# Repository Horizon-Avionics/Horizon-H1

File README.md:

# Horizon Avionics

## Building a fully open-source flight computer.

### Hardware By @Scooter Y, and @Meddy B.
### Software By: @Stars, and @Chocowafer

------

#### About:

The Goal of Horizon Avionics is to be able to build a full-fledged, and open-source flight computer for amateur rocketry. There is no such board online, and we are hoping for this board to streamline open-sourcing products instead of charging upwards of $400 for a ~$130 board.

#### Features:

- This whole board including antennas are under $150 USD.

- IMU/Baro for our sensor data.

- GPS for navigation of where the rocket landed and it's flight path.

- RF - Including a transmit tower for receiving/sending data from the rocket live during the flight.

- NAND + Micro SD Card Storage for logging.

- 3 MCU's each controlling different ascpetcs of the flight computer- MMCU, TMCU, NMCU.

- H-Bridge for servo movement.

- Working PWM for TVC and/or Reaction Wheel

- Pyro-channels for parachute deployment

  ------

#### How it's all gonna work:

For the most part, this will all be explained over on the software repo, but a short synopsis will be provided below.

In short, we have 3 micro-controllers, the MMCU, the TMCU, and the NMCU. Each one of these MCU's is responsible for a different aspect of the functionality of the flight computer.  

- **The TMCU**

​	The TMCU is responsible for a number of different things. It takes in all the raw data from the IMU, Baro and the GPS data and sending it to the MMCU via SPI for filtering and logging. It is also resposible for sending and receiving the radio packets. In-short, the TMCU does a lot of different things for this board to make room for the MMCU to do the heavy lifting.

- **The NMCU**

  The NMCU is responsible for more of the physical actions of the rocket. It's main jobs are to on boot, load the saved state, for position movements, and while in-flight, it's jobs are to take in the filtered data from the MMCU, and use it to control the Camera, servo lines, reaction wheel, and pyro-channels.

- **The MMCU**

  The MMCU is our main MCU. It's main responsibilities are to, while in flight, take in all the data from the TMCU, put it through a filter (we will be using the Kalman Filter for our board as it is the best one we have found to remove noise and such), package the data, and send it back off to the TMCU for radio sending or to the NMCU for movments. Along with sending it to the nessecary MCU's, it also sends the packaged, and filtered data to the NAND which will eventually be moved to the SD Card + the Camera footage upon landing.

------

#### Getting Started

To view the different changes between commits, check it out over on [CADLAB.io](https://cadlab.io/project/29344).

##### Checkout locally

1. `git clone https://github.com/Horizon-Avionics/Horizon-Avionics-Hardware`

2. Open the corresponding folder in KiCad 9.0

### Some Photos So Far

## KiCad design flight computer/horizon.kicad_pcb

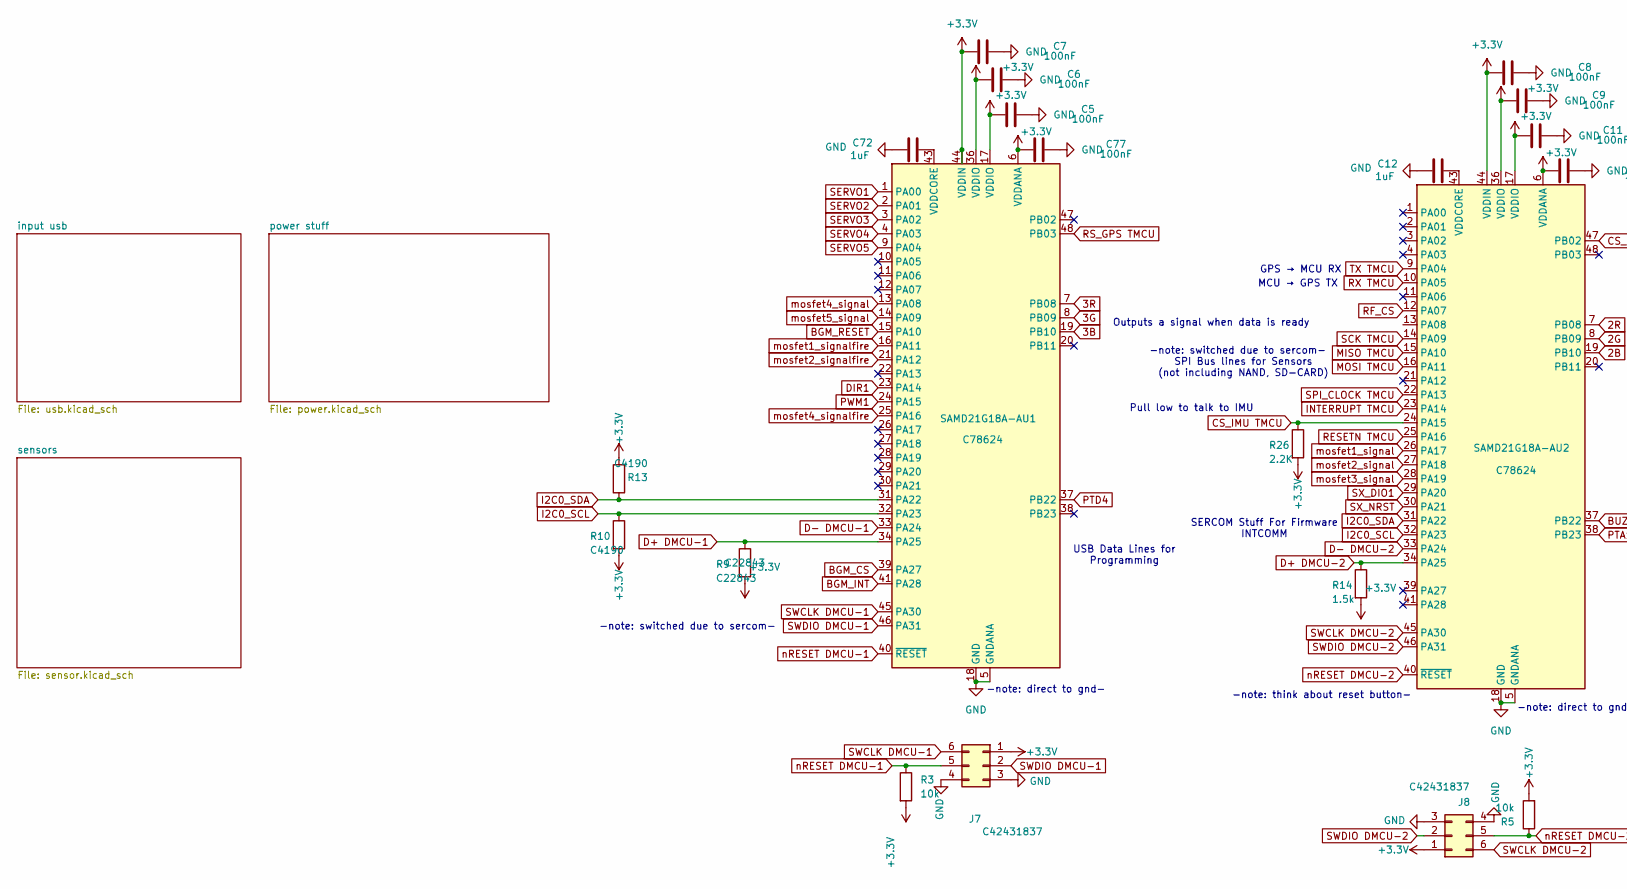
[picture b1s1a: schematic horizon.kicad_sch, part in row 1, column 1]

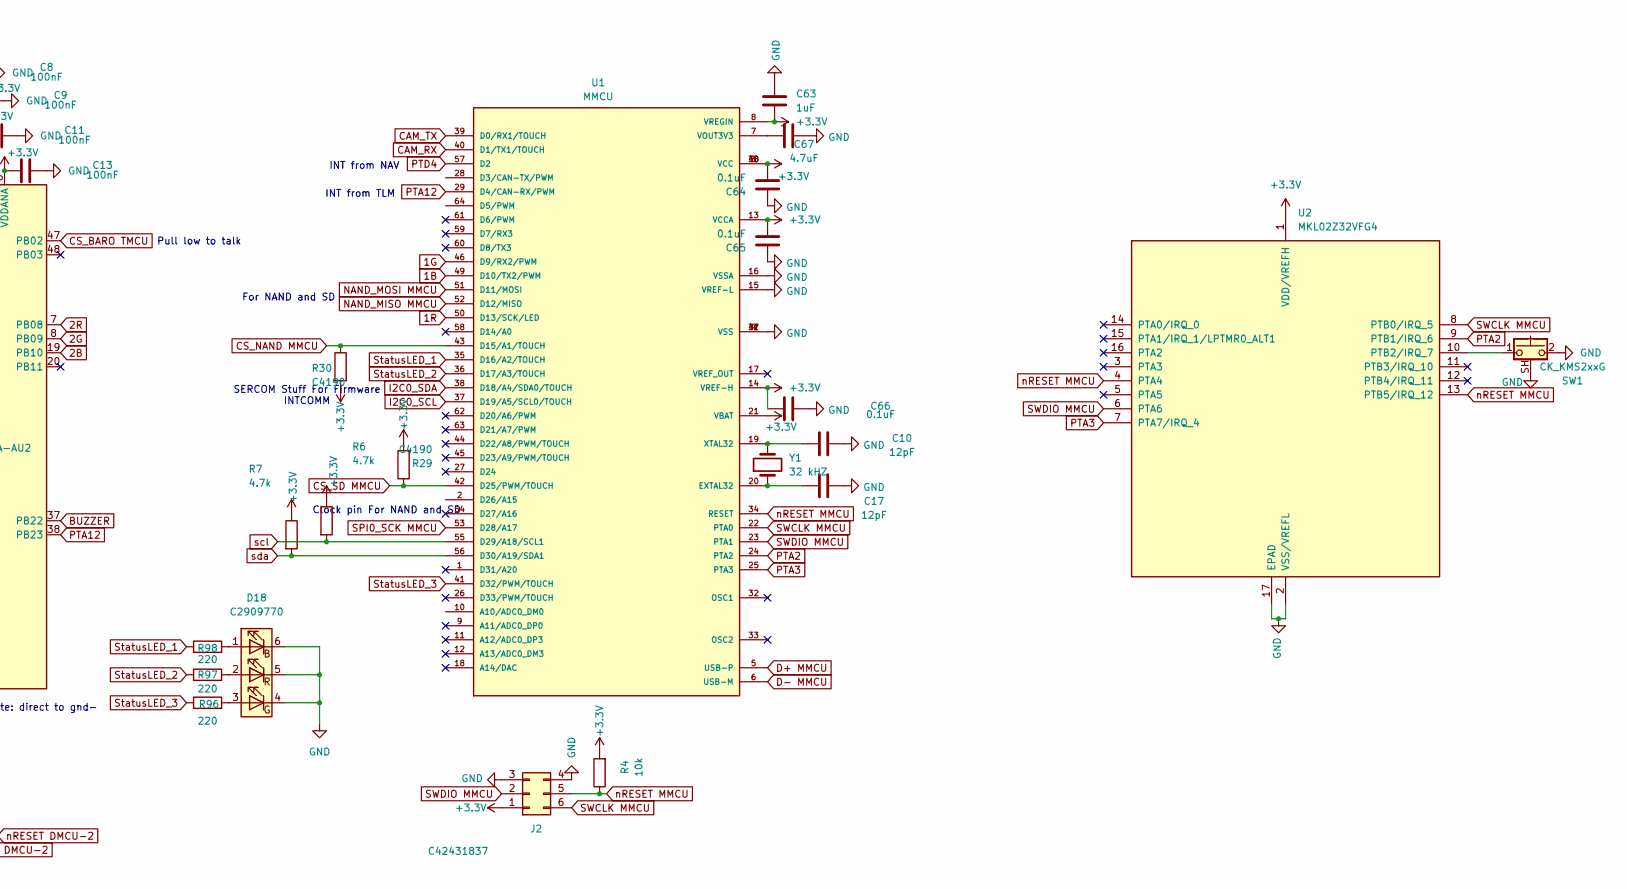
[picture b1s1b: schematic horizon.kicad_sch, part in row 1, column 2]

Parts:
C5, C6, C7, C8, C9, C11, C13, C77: 100nF; C_0603_1608Metric
C10, C17: 12pF; C_0603_1608Metric
C12, C63, C72: 1uF; C_0603_1608Metric
C64, C65, C66: 0.1uF; C_0603_1608Metric
C67: 4.7uF; C_0603_1608Metric
D18: C2909770; LED_ROHM_SMLVN6
J2, J7, J8: C42431837; PinHeader_2x03_P2.54mm_Vertical
R3, R4, R5: 10k; R_0603_1608Metric
R6, R7: 4.7k; R_0603_1608Metric
R9: C22843; R_0603_1608Metric; LCSC C22843
R10, R13, R29, R30: C4190; R_0603_1608Metric
R14: 1.5k; R_0603_1608Metric
R26: 2.2K; R_0603_1608Metric
R96, R97, R98: 220; R_0603_1608Metric
SAMD21G18A-AU1, SAMD21G18A-AU2: C78624; TQFP-48_7x7mm_P0.5mm
SW1: CK_KMS2xxG; SW_SPST_CK_KMS2xxGP
U1: MMCU; QFP50P1200X1200X160-64N
U2: MKL02Z32VFG4; QFN-16-1EP_3x3mm_P0.5mm_EP1.9x1.9mm
Y1: 32 kHZ; Crystal_AT310_D3.0mm_L10.0mm_Vertical

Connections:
1B: U1.49 (D10/TX2/PWM); also elsewhere on the board
1G: U1.46 (D9/RX2/PWM); also elsewhere on the board
1R: U1.50 (D13/SCK/LED); also elsewhere on the board
2B: SAMD21G18A-AU2.19 (PB10); also elsewhere on the board
2G: SAMD21G18A-AU2.8 (PB09); also elsewhere on the board
2R: SAMD21G18A-AU2.7 (PB08); also elsewhere on the board
3B: SAMD21G18A-AU1.19 (PB10); also elsewhere on the board
3G: SAMD21G18A-AU1.8 (PB09); also elsewhere on the board
3R: SAMD21G18A-AU1.7 (PB08); also elsewhere on the board
+3.3V: C5.2, C6.2, C7.2, C8.2, C9.2, C11.2, C13.2, C63.1, C64.1, C65.1, C66.1, C77.2, J2.1, J7.1, J8.1, R3.2, R4.2, R5.2, R6.1, R7.1, R9.2, R10.2, R13.2, R14.2, R26.2, R29.2, R30.2, SAMD21G18A-AU1.6 (VDDANA), SAMD21G18A-AU1.17 (VDDIO), SAMD21G18A-AU1.36 (VDDIO), SAMD21G18A-AU1.44 (VDDIN), SAMD21G18A-AU2.6 (VDDANA), SAMD21G18A-AU2.17 (VDDIO), SAMD21G18A-AU2.36 (VDDIO), SAMD21G18A-AU2.44 (VDDIN), U1.3 (VCC), U1.8 (VREGIN), U1.13 (VCCA), U1.14 (VREF-H), U1.21 (VBAT), U1.30 (VCC), U1.48 (VCC), U2.1 (VDD/VREFH); also elsewhere on the board
BGM_CS: SAMD21G18A-AU1.39 (PA27); also elsewhere on the board
BGM_INT: SAMD21G18A-AU1.41 (PA28); also elsewhere on the board
BGM_RESET: SAMD21G18A-AU1.15 (PA10); also elsewhere on the board
BUZZER: SAMD21G18A-AU2.37 (PB22); also elsewhere on the board
CAM_RX: U1.40 (D1/TX1/TOUCH); also elsewhere on the board
CAM_TX: U1.39 (D0/RX1/TOUCH); also elsewhere on the board
CS_BARO TMCU: SAMD21G18A-AU2.47 (PB02); also elsewhere on the board
CS_IMU TMCU: R26.1, SAMD21G18A-AU2.24 (PA15); also elsewhere on the board
CS_NAND MMCU: R30.1, U1.43 (D15/A1/TOUCH); also elsewhere on the board
CS_SD MMCU: R29.1, U1.42 (D25/PWM/TOUCH); also elsewhere on the board
D+ DMCU-1: R9.1, SAMD21G18A-AU1.34 (PA25); also elsewhere on the board
D+ DMCU-2: R14.1, SAMD21G18A-AU2.34 (PA25); also elsewhere on the board
D+ MMCU: U1.5 (USB-P); also elsewhere on the board
D- DMCU-1: SAMD21G18A-AU1.33 (PA24); also elsewhere on the board
D- DMCU-2: SAMD21G18A-AU2.33 (PA24); also elsewhere on the board
D- MMCU: U1.6 (USB-M); also elsewhere on the board
DIR1: SAMD21G18A-AU1.23 (PA14)
GND: C5.1, C6.1, C7.1, C8.1, C9.1, C10.2, C11.1, C12.1, C13.1, C17.2, C63.2, C64.2, C65.2, C66.2, C67.2, C72.1, C77.1, D18.4 (GK), D18.5 (RK), D18.6 (BK), J2.3, J2.4, J7.3, J7.4, J8.3, J8.4, SAMD21G18A-AU1.5 (GNDANA), SAMD21G18A-AU1.18 (GND), SAMD21G18A-AU1.35 (GND), SAMD21G18A-AU1.42 (GND), SAMD21G18A-AU2.5 (GNDANA), SAMD21G18A-AU2.18 (GND), SAMD21G18A-AU2.35 (GND), SAMD21G18A-AU2.42 (GND), SW1.2, SW1.SH (B), U1.4 (VSS), U1.15 (VREF-L), U1.16 (VSSA), U1.31 (VSS), U1.47 (VSS), U2.2 (VSS/VREFL), U2.17 (EPAD); also elsewhere on the board
I2C0_SCL: R10.1, SAMD21G18A-AU1.32 (PA23), SAMD21G18A-AU2.32 (PA23), U1.37 (D19/A5/SCL0/TOUCH); also elsewhere on the board
I2C0_SDA: R13.1, SAMD21G18A-AU1.31 (PA22), SAMD21G18A-AU2.31 (PA22), U1.38 (D18/A4/SDA0/TOUCH); also elsewhere on the board
INTERRUPT TMCU: SAMD21G18A-AU2.23 (PA14); also elsewhere on the board
MISO TMCU: SAMD21G18A-AU2.15 (PA10); also elsewhere on the board
MOSI TMCU: SAMD21G18A-AU2.16 (PA11); also elsewhere on the board
NAND_MISO MMCU: U1.52 (D12/MISO); also elsewhere on the board
NAND_MOSI MMCU: U1.51 (D11/MOSI); also elsewhere on the board
unnamed: D18.1 (BA), R98.2
unnamed: D18.3 (GA), R96.2
unnamed: D18.2 (RA), R97.2
unnamed: C72.2, SAMD21G18A-AU1.43 (VDDCORE)
unnamed: C12.2, SAMD21G18A-AU2.43 (VDDCORE)
unnamed: C17.1, U1.20 (EXTAL32), Y1.1
unnamed: C67.1, U1.7 (VOUT3V3)
unnamed: C10.1, U1.19 (XTAL32), Y1.2
unnamed: SW1.1, U2.10 (PTB2/IRQ_7)
PTA2: U1.24 (PTA2), U2.9 (PTB1/IRQ_6)
PTA3: U1.25 (PTA3), U2.7 (PTA7/IRQ_4)
PTA12: SAMD21G18A-AU2.38 (PB23), U1.29 (D4/CAN-RX/PWM)
PTD4: SAMD21G18A-AU1.37 (PB22), U1.57 (D2)
PWM1: SAMD21G18A-AU1.24 (PA15)
RESETN TMCU: SAMD21G18A-AU2.25 (PA16)
RF_CS: SAMD21G18A-AU2.12 (PA07); also elsewhere on the board
RS_GPS TMCU: SAMD21G18A-AU1.48 (PB03); also elsewhere on the board
RX TMCU: SAMD21G18A-AU2.10 (PA05); also elsewhere on the board
SCK TMCU: SAMD21G18A-AU2.14 (PA09); also elsewhere on the board
SERVO1: SAMD21G18A-AU1.1 (PA00); also elsewhere on the board
SERVO2: SAMD21G18A-AU1.2 (PA01); also elsewhere on the board
SERVO3: SAMD21G18A-AU1.3 (PA02); also elsewhere on the board
SERVO4: SAMD21G18A-AU1.4 (PA03); also elsewhere on the board
SERVO5: SAMD21G18A-AU1.9 (PA04); also elsewhere on the board
SPI0_SCK MMCU: U1.53 (D28/A17); also elsewhere on the board
SPI_CLOCK TMCU: SAMD21G18A-AU2.22 (PA13); also elsewhere on the board
SWCLK DMCU-1: J7.6, SAMD21G18A-AU1.45 (PA30)
SWCLK DMCU-2: J8.6, SAMD21G18A-AU2.45 (PA30)
SWCLK MMCU: J2.6, U1.22 (PTA0), U2.8 (PTB0/IRQ_5)
SWDIO DMCU-1: J7.2, SAMD21G18A-AU1.46 (PA31)
SWDIO DMCU-2: J8.2, SAMD21G18A-AU2.46 (PA31)
SWDIO MMCU: J2.2, U1.23 (PTA1), U2.6 (PTA6)
SX_DIO1: SAMD21G18A-AU2.29 (PA20); also elsewhere on the board
SX_NRST: SAMD21G18A-AU2.30 (PA21); also elsewhere on the board
StatusLED_1: R98.1, U1.35 (D16/A2/TOUCH)
StatusLED_2: R97.1, U1.36 (D17/A3/TOUCH)
StatusLED_3: R96.1, U1.41 (D32/PWM/TOUCH)
TX TMCU: SAMD21G18A-AU2.9 (PA04); also elsewhere on the board
mosfet1_signal: SAMD21G18A-AU2.26 (PA17)
mosfet1_signalfire: SAMD21G18A-AU1.16 (PA11); also elsewhere on the board
mosfet2_signal: SAMD21G18A-AU2.27 (PA18)
mosfet2_signalfire: SAMD21G18A-AU1.21 (PA12); also elsewhere on the board
mosfet3_signal: SAMD21G18A-AU2.28 (PA19)
mosfet4_signal: SAMD21G18A-AU1.13 (PA08)
mosfet4_signalfire: SAMD21G18A-AU1.25 (PA16)
mosfet5_signal: SAMD21G18A-AU1.14 (PA09)
nRESET DMCU-1: J7.5, R3.1, SAMD21G18A-AU1.40 (~RESET)
nRESET DMCU-2: J8.5, R5.1, SAMD21G18A-AU2.40 (~RESET)
nRESET MMCU: J2.5, R4.1, U1.34 (RESET), U2.4 (PTA4), U2.13 (PTB5/IRQ_12)
scl: R6.2, U1.55 (D29/A18/SCL1)
sda: R7.2, U1.56 (D30/A19/SDA1)

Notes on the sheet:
SERCOM Stuff For Firmware INTCOMM
-note: direct to gnd-
For NAND and SD
-note: switched due to sercom-
Pull low to talk to IMU
INT from TLM
Pull low to talk
GPS → MCU RX
Clock pin For NAND and SD
MCU → GPS TX
Outputs a signal when data is ready
-note: think about reset button-
INT from NAV
USB Data Lines for Programming
SPI Bus lines for Sensors (not including NAND, SD-CARD)

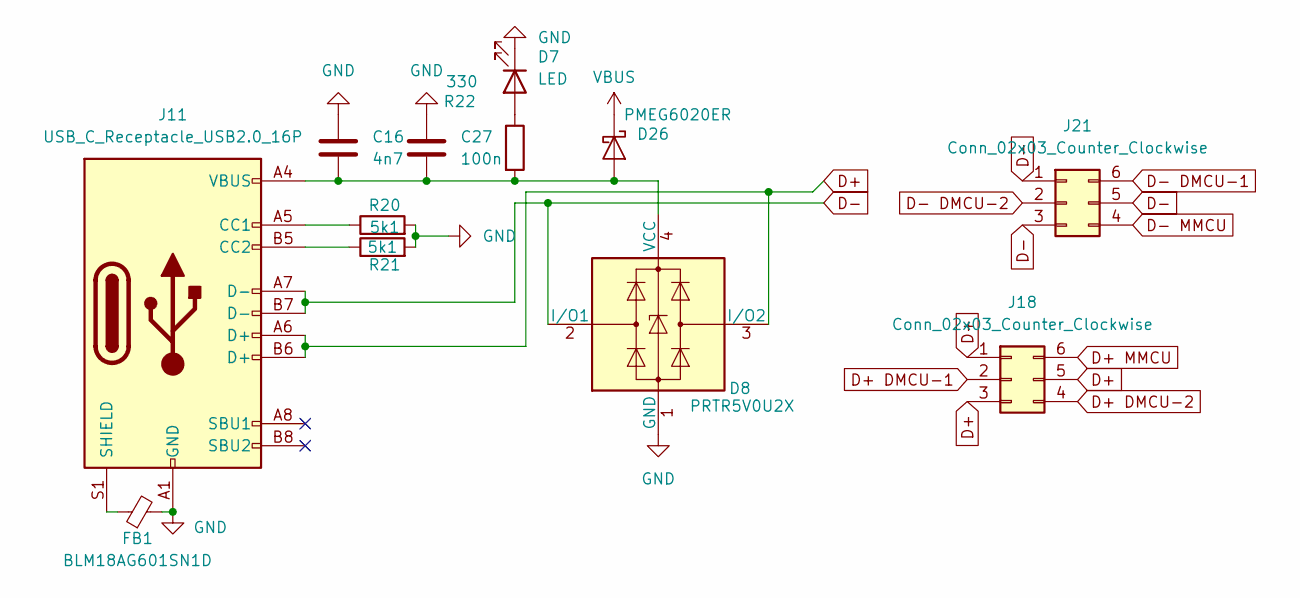
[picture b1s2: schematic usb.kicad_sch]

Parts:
C16: 4n7; C_0603_1608Metric
C27: 100n; C_0603_1608Metric
D7: LED; LED_0603_1608Metric
D8: PRTR5V0U2X; SOT-143
D26: PMEG6020ER; Nexperia_CFP3_SOD-123W
FB1: BLM18AG601SN1D; R_0603_1608Metric
J11: USB_C_Receptacle_USB2.0_16P; USB_C_Receptacle_GCT_USB4105-xx-A_16P_TopMnt_Horizontal
J18, J21: Conn_02x03_Counter_Clockwise; PinHeader_2x03_P2.54mm_Vertical
R20, R21: 5k1; R_0603_1608Metric
R22: 330; R_0603_1608Metric

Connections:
D+: D8.3 (I/O2), J11.A6 (D+), J11.B6 (D+), J18.1, J18.3, J18.5
D+ DMCU-1: J18.2; also elsewhere on the board
D+ DMCU-2: J18.4; also elsewhere on the board
D+ MMCU: J18.6; also elsewhere on the board
D-: D8.2 (I/O1), J11.A7 (D-), J11.B7 (D-), J21.1, J21.3, J21.5
D- DMCU-1: J21.6; also elsewhere on the board
D- DMCU-2: J21.2; also elsewhere on the board
D- MMCU: J21.4; also elsewhere on the board
GND: C16.1, C27.1, D7.1 (K), D8.1 (GND), FB1.2, J11.A1 (GND), J11.A12 (GND), J11.B1 (GND), J11.B12 (GND), R20.2, R21.2; also elsewhere on the board
unnamed: D7.2 (A), R22.1
unnamed: C16.2, C27.2, D8.4 (VCC), D26.2 (A), J11.A4 (VBUS), J11.A9 (VBUS), J11.B4 (VBUS), J11.B9 (VBUS), R22.2
unnamed: J11.A5 (CC1), R20.1
unnamed: J11.B5 (CC2), R21.1
unnamed: FB1.1, J11.S1 (SHIELD)
POWAAAA: D26.1 (K); also elsewhere on the board

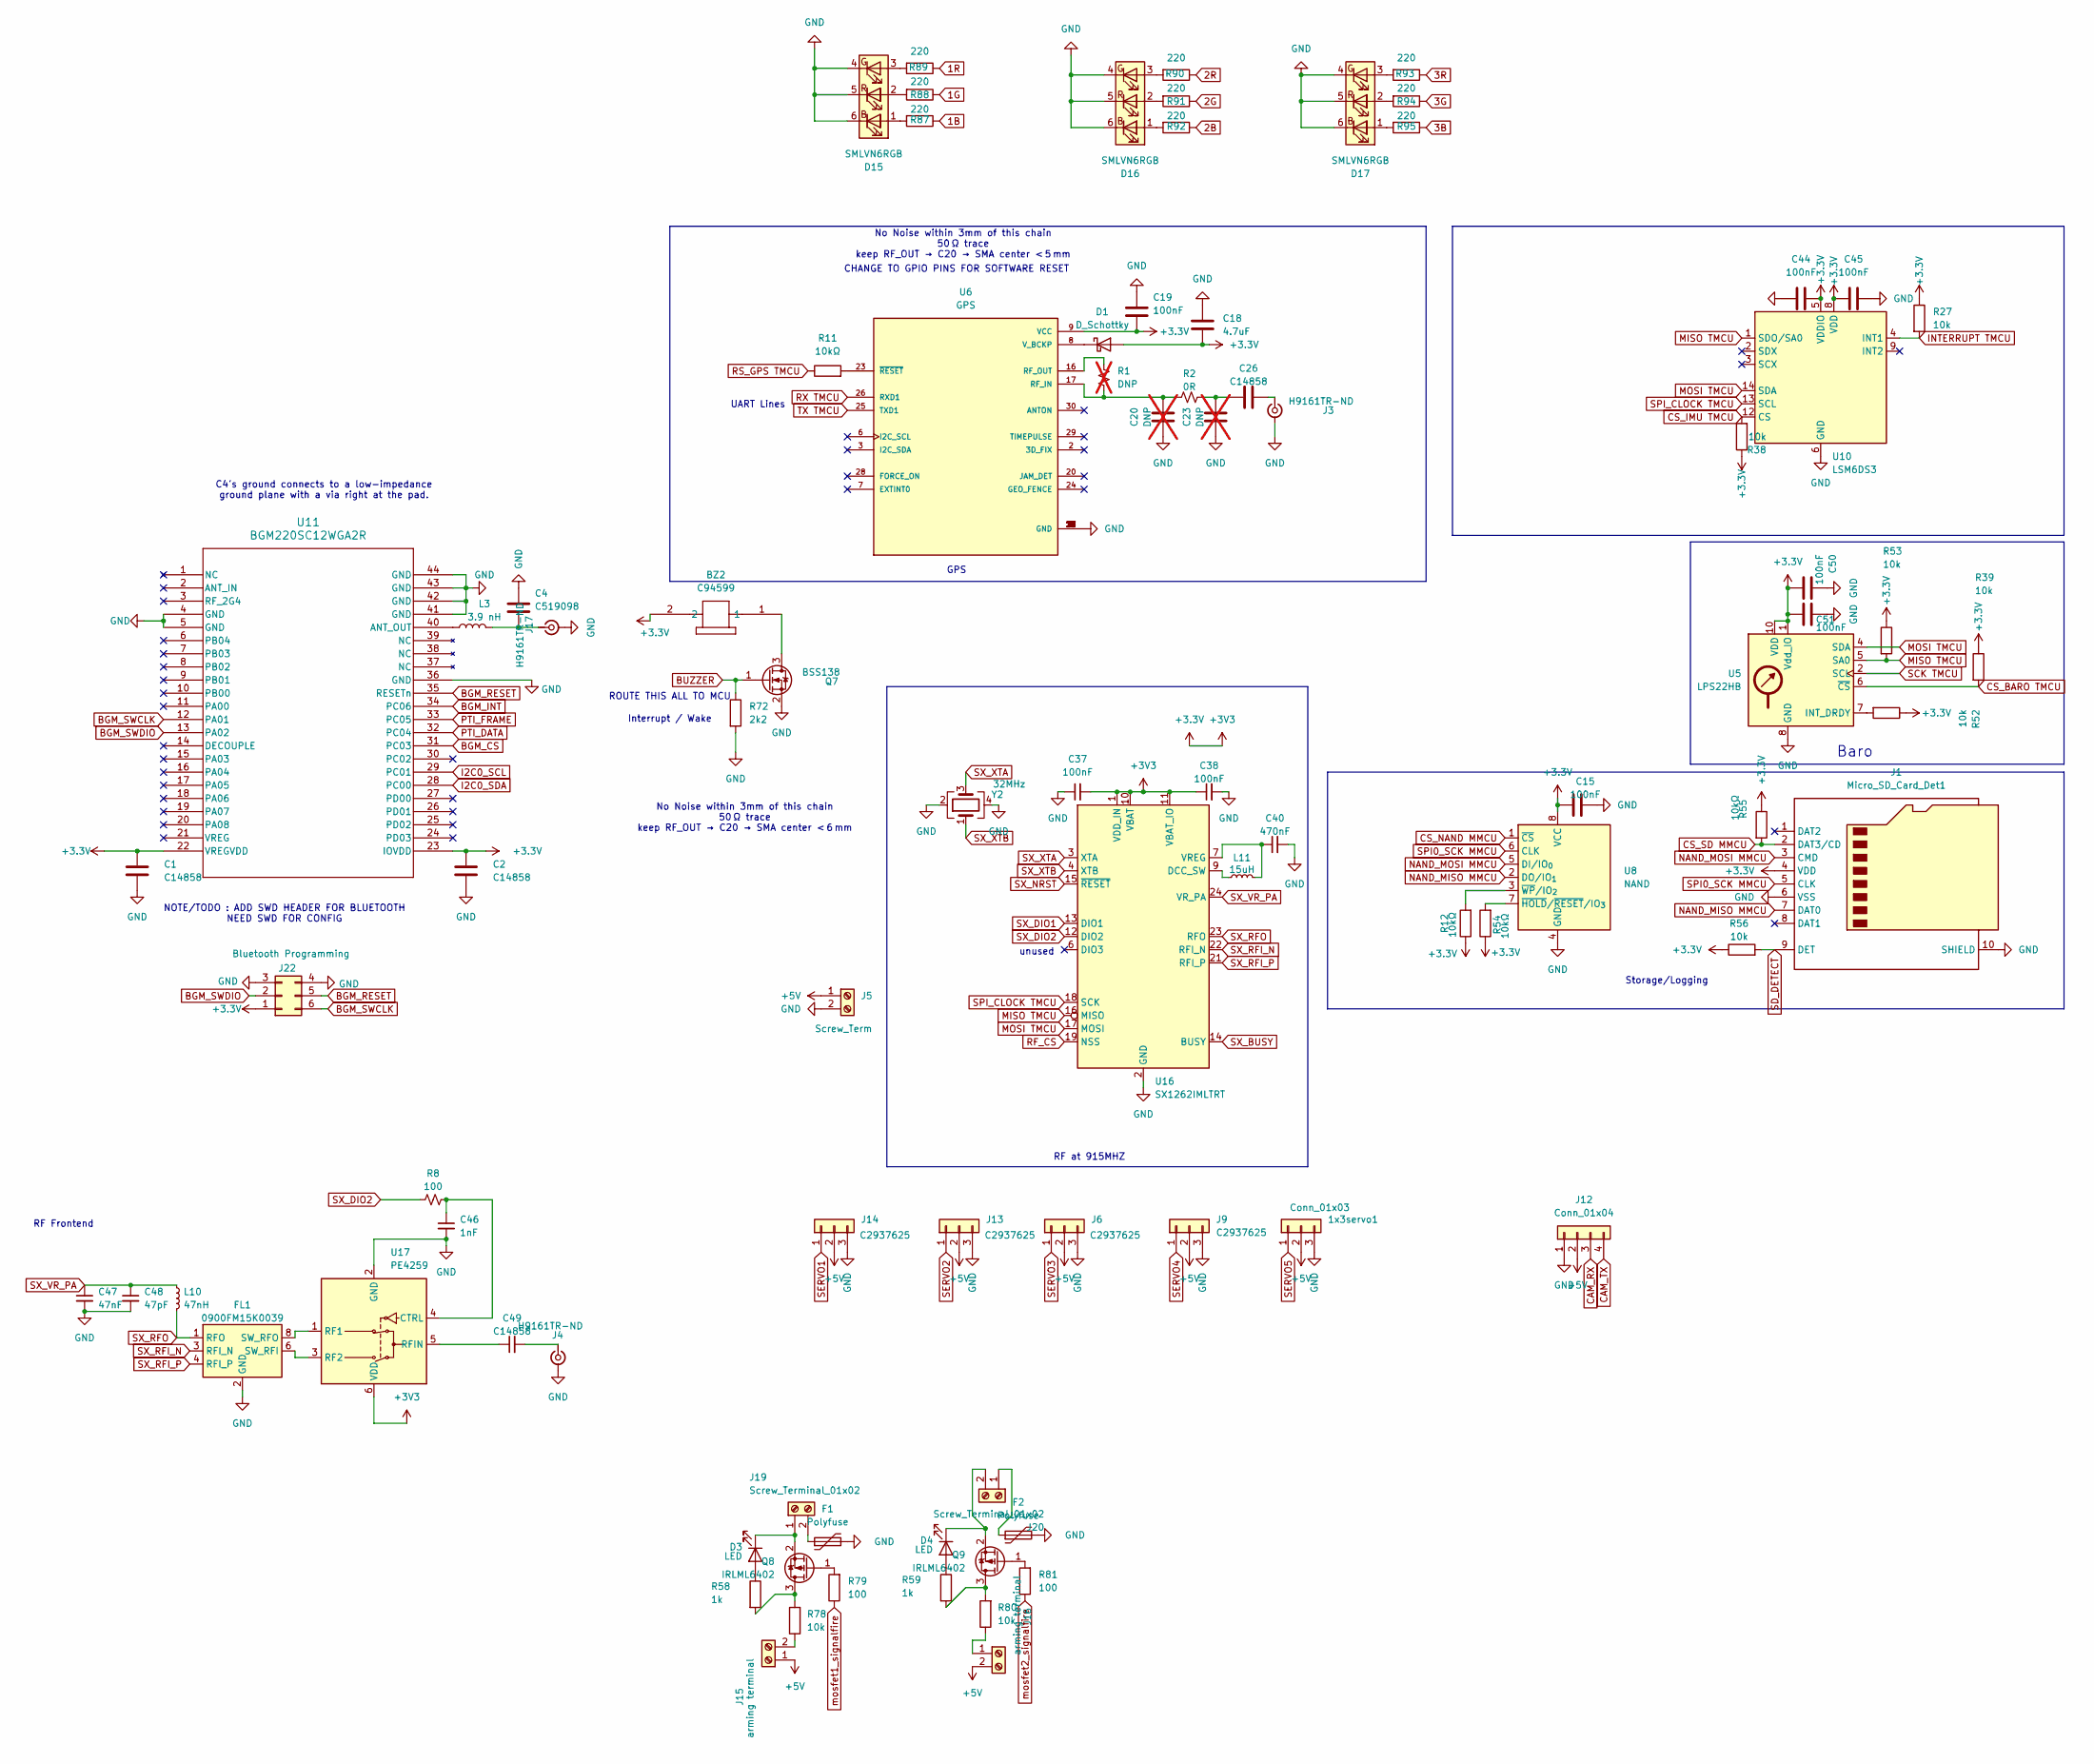
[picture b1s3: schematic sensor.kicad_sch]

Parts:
1x3servo1: Conn_01x03; PinHeader_1x03_P2.54mm_Vertical
BZ2: C94599; MLT-8530_JHE
C1, C2, C26: C14858; C_0603_1608Metric
C4: C519098; C_0603_1608Metric
C15, C19, C44, C45, C50, C51: 100nF; C_0603_1608Metric
C18: 4.7uF; C_0603_1608Metric
C20, C23: DNP; C_0603_1608Metric; not fitted
C37, C38: 100nF; C_0603_1608Metric; LCSC Part C14663
C40: 470nF; C_0603_1608Metric; LCSC Part C1623
C46: 1nF; C_0603_1608Metric; LCSC Part C100040
C47: 47nF; C_0603_1608Metric; LCSC Part C107093
C48: 47pF; C_0603_1608Metric; LCSC Part C105622
C49: C14858; C_0603_1608Metric; LCSC Part C14665
D1: D_Schottky; D_0603_1608Metric
D3, D4: LED; LED_0603_1608Metric
D15, D16, D17: SMLVN6RGB; LED_ROHM_SMLVN6
F1, F2: Polyfuse; Fuse_0603_1608Metric
FL1: 0900FM15K0039; Balun_Johanson_0900FM15K0039; LCSC Part C5224443
J1: Micro_SD_Card_Det1; microSD_HC_Hirose_DM3D-SF
J3, J4, J17: H9161TR-ND; U.FL_Hirose_U.FL-R-SMT-1_Vertical
J5: Screw_Term; TerminalBlock_Phoenix_MPT-0,5-2-2.54_1x02_P2.54mm_Horizontal
J6, J9, J13, J14: C2937625; PinHeader_1x03_P2.54mm_Vertical
J12: Conn_01x04; PinHeader_1x04_P2.54mm_Vertical
J15, J16: arming terminal; TerminalBlock_Phoenix_MPT-0,5-2-2.54_1x02_P2.54mm_Horizontal
J19, J20: Screw_Terminal_01x02; TerminalBlock_Phoenix_MPT-0,5-2-2.54_1x02_P2.54mm_Horizontal
J22: Bluetooth Programming; PinHeader_2x03_P2.54mm_Vertical
L3: 3.9 nH; L_0603_1608Metric
L10: 47nH; L_0603_1608Metric; LCSC Part C285885
L11: 15uH; L_0805_2012Metric; LCSC Part C383402
Q7: BSS138; SOT-23
Q8, Q9: IRLML6402; SOT-23
R1: DNP; R_0603_1608Metric; not fitted
R2: 0R; R_0603_1608Metric
R8: 100; R_0603_1608Metric; LCSC Part C105588
R11, R12, R54, R55: 10kΩ; R_0603_1608Metric
R27, R38, R39, R52, R53, R56, R78, R80: 10k; R_0603_1608Metric
R58, R59: 1k; R_0603_1608Metric
R72: 2k2; R_0603_1608Metric
R79, R81: 100; R_0603_1608Metric
R87, R88, R89, R90, R91, R92, R93, R94, R95: 220; R_0603_1608Metric
U5: LPS22HB; ST_HLGA-10_2x2mm_P0.5mm_LayoutBorder3x2y
U6: GPS; Quectel_L96; DigiKey_Part_Number 2958-L96-M33TR-ND
U8: NAND; SOIC-8_5.3x5.3mm_P1.27mm
U10: LSM6DS3; LGA-14_3x2.5mm_P0.5mm_LayoutBorder3x4y
U11: BGM220SC12WGA2R; BGM220S_SIL
U16: SX1262IMLTRT; QFN-24-1EP_4x4mm_P0.5mm_EP2.6x2.6mm; LCSC Part C191341
U17: PE4259; SOT-363_SC-70-6; LCSC Part C470892
Y2: 32MHz; Crystal_SMD_3225-4Pin_3.2x2.5mm; LCSC Part C37635386

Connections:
1B: R87.1; also elsewhere on the board
1G: R88.1; also elsewhere on the board
1R: R89.1; also elsewhere on the board
2B: R92.1; also elsewhere on the board
2G: R91.1; also elsewhere on the board
2R: R90.1; also elsewhere on the board
3B: R95.1; also elsewhere on the board
3G: R94.1; also elsewhere on the board
3R: R93.1; also elsewhere on the board
+3.3V: BZ2.2, C1.2, C2.2, C15.1, C18.2, C19.2, C37.2, C38.1, C44.2, C45.2, C50.2, C51.2, D1.2 (A), J1.4 (VDD), J22.1, R12.1, R27.1, R38.1, R39.1, R52.1, R53.1, R54.1, R55.1, R56.1, U5.1 (Vdd_IO), U5.10 (VDD), U6.9 (VCC), U8.8 (VCC), U10.5 (VDDIO), U10.8 (VDD), U11.22 (VREGVDD), U11.23 (IOVDD), U16.1 (VDD_IN), U16.10 (VBAT), U16.11 (VBAT_IO), U17.6 (VDD); also elsewhere on the board
+5V: 1x3servo1.2, J5.1, J6.2, J9.2, J12.2, J13.2, J14.2, J15.1, J16.2; also elsewhere on the board
BGM_CS: U11.31 (PC03); also elsewhere on the board
BGM_INT: U11.34 (PC06); also elsewhere on the board
BGM_RESET: J22.5, U11.35 (RESETn); also elsewhere on the board
BGM_SWCLK: J22.6, U11.12 (PA01)
BGM_SWDIO: J22.2, U11.13 (PA02)
BUZZER: Q7.1 (G), R72.1; also elsewhere on the board
CAM_RX: J12.3; also elsewhere on the board
CAM_TX: J12.4; also elsewhere on the board
CS_BARO TMCU: R39.2, U5.6 (~CS); also elsewhere on the board
CS_IMU TMCU: R38.2, U10.12 (CS); also elsewhere on the board
CS_NAND MMCU: U8.1 (~CS); also elsewhere on the board
CS_SD MMCU: J1.2 (DAT3/CD), R55.2; also elsewhere on the board
GND: 1x3servo1.3, C1.1, C2.1, C4.1, C15.2, C18.1, C19.1, C20.2, C23.2, C37.1, C38.2, C40.2, C44.1, C45.1, C46.2, C47.2, C48.2, C50.1, C51.1, D15.4 (GK), D15.5 (RK), D15.6 (BK), D16.4 (GK), D16.5 (RK), D16.6 (BK), D17.4 (GK), D17.5 (RK), D17.6 (BK), F1.2, F2.2, FL1.2 (GND), FL1.5 (GND), FL1.7 (GND), FL1.9 (GND), FL1.10 (GND), J1.6 (VSS), J1.10 (SHIELD), J3.2 (Ext), J4.2 (Ext), J5.2, J6.3, J9.3, J12.1, J13.3, J14.3, J17.2 (Ext), J22.3, J22.4, Q7.2 (S), R72.2, U5.3 (GND), U5.8 (GND), U5.9 (GND), U6.4 (GND), U6.5 (GND), U6.10 (GND), U6.11 (GND), U6.12 (GND), U6.13 (GND), U6.14 (GND), U6.15 (GND), U6.18 (GND), U6.19 (GND), U6.21 (GND), U6.22 (GND), U6.27 (GND), U6.31 (GND), U8.4 (GND), U10.6 (GND), U10.7 (GND), U11.4 (GND), U11.5 (GND), U11.36 (GND), U11.41 (GND), U11.42 (GND), U11.43 (GND), U11.44 (GND), U16.2 (GND), U16.5 (GND), U16.8 (GND), U16.20 (GND), U16.25 (GND), U17.2 (GND), Y2.2, Y2.4; also elsewhere on the board
I2C0_SCL: U11.29 (PC01); also elsewhere on the board
I2C0_SDA: U11.28 (PC00); also elsewhere on the board
INTERRUPT TMCU: R27.2, U10.4 (INT1); also elsewhere on the board
MISO TMCU: R53.2, U5.5 (SA0), U10.1 (SDO/SA0), U16.16 (MISO); also elsewhere on the board
MOSI TMCU: U5.4 (SDA), U10.14 (SDA), U16.17 (MOSI); also elsewhere on the board
NAND_MISO MMCU: J1.7 (DAT0), U8.2 (DO/IO_{1}); also elsewhere on the board
NAND_MOSI MMCU: J1.3 (CMD), U8.5 (DI/IO_{0}); also elsewhere on the board
unnamed: C23.1, C26.2, R2.2
unnamed: D1.1 (K), U6.8 (V_BCKP)
unnamed: D3.2 (A), R58.1
unnamed: D3.1 (K), J19.1, Q8.2 (S)
unnamed: D4.2 (A), R59.1
unnamed: D4.1 (K), J20.2, Q9.2 (S)
unnamed: D15.1 (BA), R87.2
unnamed: D15.3 (GA), R89.2
unnamed: D15.2 (RA), R88.2
unnamed: D16.1 (BA), R92.2
unnamed: D16.3 (GA), R90.2
unnamed: D16.2 (RA), R91.2
unnamed: D17.1 (BA), R95.2
unnamed: D17.3 (GA), R93.2
unnamed: D17.2 (RA), R94.2
unnamed: FL1.6 (SW_RFI), U17.3 (RF2)
unnamed: FL1.8 (SW_RFO), U17.1 (RF1)
unnamed: C26.1, J3.1 (In)
unnamed: C49.2, J4.1 (In)
unnamed: J15.2, R78.1
unnamed: J16.1, R80.1
unnamed: C4.2, J17.1 (In), L3.2
unnamed: F1.1, J19.2
unnamed: F2.1, J20.1
unnamed: BZ2.1, Q7.3 (D)
unnamed: Q8.3 (D), R58.2, R78.2
unnamed: Q8.1 (G), R79.2
unnamed: Q9.3 (D), R59.2, R80.2
unnamed: Q9.1 (G), R81.2
unnamed: R52.2, U5.7 (INT_DRDY)
unnamed: C20.1, R1.2, R2.1, U6.17 (RF_IN)
unnamed: R1.1, U6.16 (RF_OUT)
unnamed: R11.2, U6.23 (~RESET)
unnamed: R54.2, U8.7 (~HOLD/~RESET/IO_{3})
unnamed: R12.2, U8.3 (~WP/IO_{2})
unnamed: L3.1, U11.40 (ANT_OUT)
unnamed: L11.1, U16.9 (DCC_SW)
unnamed: C40.1, L11.2, U16.7 (VREG)
unnamed: C46.1, R8.2, U17.4 (CTRL)
unnamed: C49.1, U17.5 (RFIN)
PTI_DATA: U11.32 (PC04)
PTI_FRAME: U11.33 (PC05)
RF_CS: U16.19 (NSS); also elsewhere on the board
RS_GPS TMCU: R11.1; also elsewhere on the board
RX TMCU: U6.26 (RXD1); also elsewhere on the board
SCK TMCU: U5.2 (SCL); also elsewhere on the board
SD_DETECT: J1.9 (DET), R56.2
SERVO1: J14.1; also elsewhere on the board
SERVO2: J13.1; also elsewhere on the board
SERVO3: J6.1; also elsewhere on the board
SERVO4: J9.1; also elsewhere on the board
SERVO5: 1x3servo1.1; also elsewhere on the board
SPI0_SCK MMCU: J1.5 (CLK), U8.6 (CLK); also elsewhere on the board
SPI_CLOCK TMCU: U10.13 (SCL), U16.18 (SCK); also elsewhere on the board
SX_BUSY: U16.14 (BUSY)
SX_DIO1: U16.13 (DIO1); also elsewhere on the board
SX_DIO2: R8.1, U16.12 (DIO2)
SX_NRST: U16.15 (~RESET); also elsewhere on the board
SX_RFI_N: FL1.3 (RFI_N), U16.22 (RFI_N)
SX_RFI_P: FL1.4 (RFI_P), U16.21 (RFI_P)
SX_RFO: FL1.1 (RFO), L10.2, U16.23 (RFO)
SX_VR_PA: C47.1, C48.1, L10.1, U16.24 (VR_PA)
SX_XTA: U16.3 (XTA), Y2.3
SX_XTB: U16.4 (XTB), Y2.1
TX TMCU: U6.25 (TXD1); also elsewhere on the board
mosfet1_signalfire: R79.1; also elsewhere on the board
mosfet2_signalfire: R81.1; also elsewhere on the board

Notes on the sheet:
GPS
UART Lines
C4's ground connects to a low-impedance ground plane with a via right at the pad.
NOTE/TODO : ADD SWD HEADER FOR BLUETOOTH NEED SWD FOR CONFIG
Storage/Logging
unused
CHANGE TO GPIO PINS FOR SOFTWARE RESET
ROUTE THIS ALL TO MCU
Baro
Interrupt / Wake
No Noise within 3mm of this chain 50 Ω trace keep RF_OUT → C20 → SMA center < 6 mm
RF Frontend
RF at 915MHZ
No Noise within 3mm of this chain 50 Ω trace keep RF_OUT → C20 → SMA center < 5 mm

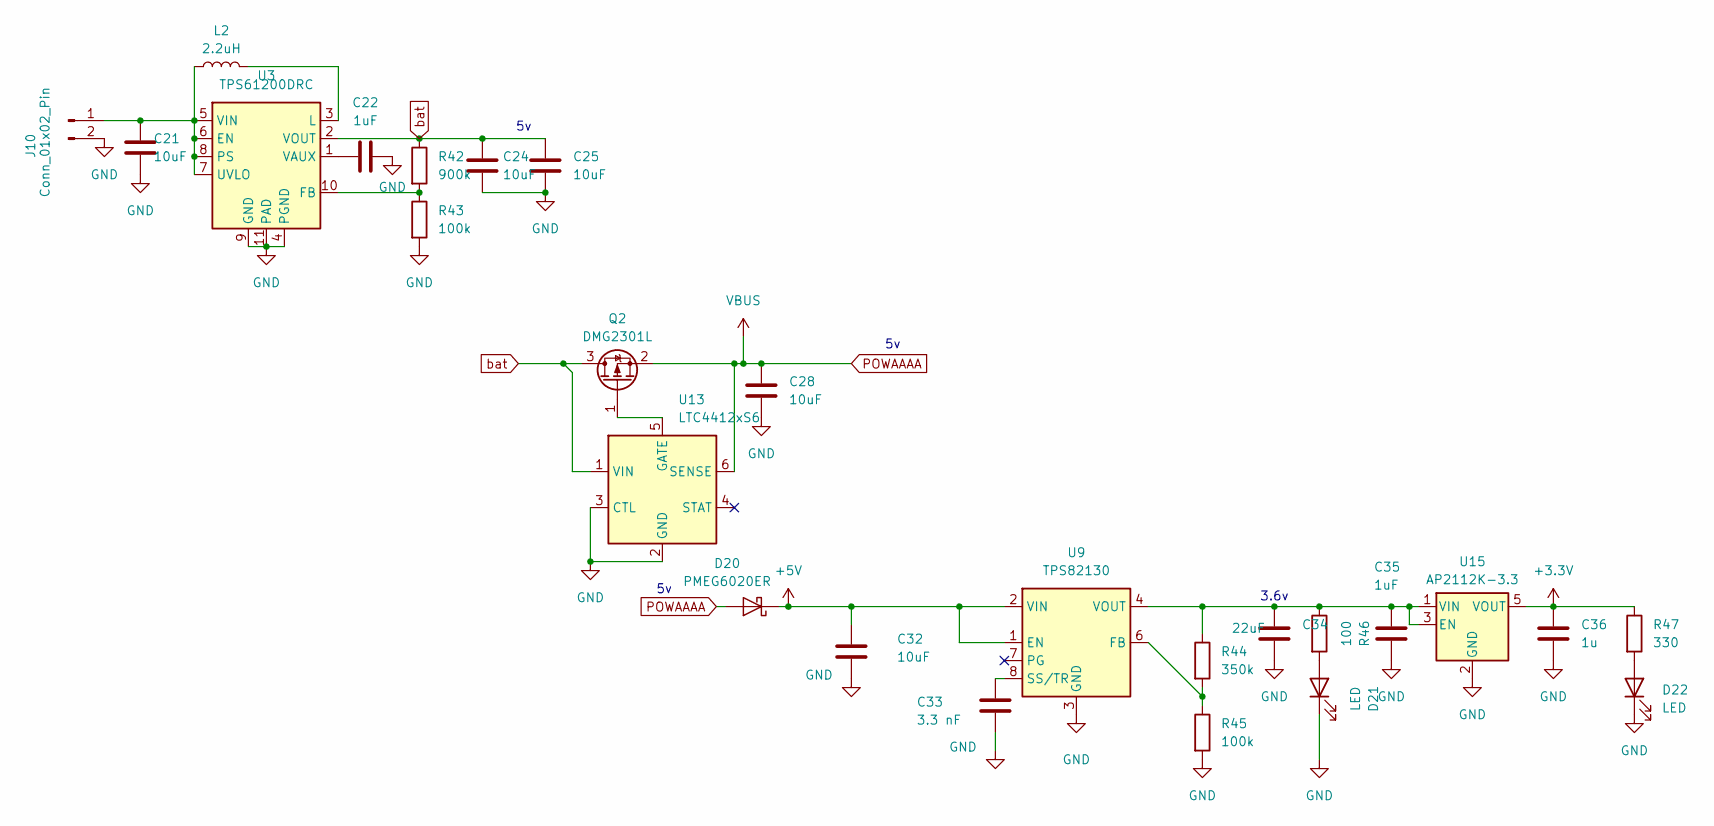
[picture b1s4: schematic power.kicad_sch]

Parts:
C21, C24, C25, C28, C32: 10uF; C_0603_1608Metric
C22, C35: 1uF; C_0603_1608Metric
C33: 3.3 nF; C_0603_1608Metric
C34: 22uF; C_0603_1608Metric
C36: 1u; C_0603_1608Metric
D20: PMEG6020ER; Nexperia_CFP3_SOD-123W
D21, D22: LED; LED_0603_1608Metric
J10: Conn_01x02_Pin; TerminalBlock_Phoenix_MPT-0,5-2-2.54_1x02_P2.54mm_Horizontal
L2: 2.2uH; L_APV_ANR4018
Q2: DMG2301L; SOT-23
R42: 900k; R_0603_1608Metric
R43, R45: 100k; R_0603_1608Metric
R44: 350k; R_0603_1608Metric
R46: 100; R_0603_1608Metric
R47: 330; R_0603_1608Metric
U3: TPS61200DRC; Texas_S-PVSON-N10_ThermalVias
U9: TPS82130; Texas_SIL0008D_MicroSiP-8-1EP_2.8x3mm_P0.65mm_EP1.1x1.9mm_T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
U13: LTC4412xS6; TSOT-23-6
U15: AP2112K-3.3; SOT-23-5

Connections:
+3.3V: C36.1, R47.1, U15.5 (VOUT); also elsewhere on the board
+5V: C32.1, D20.1 (K), U9.1 (EN), U9.2 (VIN); also elsewhere on the board
GND: C21.2, C22.2, C24.2, C25.2, C28.2, C32.2, C33.2, C34.2, C35.2, C36.2, D21.1 (K), D22.1 (K), J10.2, R43.2, R45.2, U3.4 (PGND), U3.9 (GND), U3.11 (PAD), U9.3 (GND), U9.9 (GND), U13.2 (GND), U13.3 (CTL), U15.2 (GND); also elsewhere on the board
unnamed: D21.2 (A), R46.2
unnamed: D22.2 (A), R47.2
unnamed: C21.1, J10.1, L2.1, U3.5 (VIN), U3.6 (EN), U3.7 (UVLO), U3.8 (PS)
unnamed: Q2.1 (G), U13.5 (GATE)
unnamed: R42.2, R43.1, U3.10 (FB)
unnamed: L2.2, U3.3 (L)
unnamed: C22.1, U3.1 (VAUX)
unnamed: R44.2, R45.1, U9.6 (FB)
unnamed: C33.1, U9.8 (SS/TR)
unnamed: C34.1, C35.1, R44.1, R46.1, U9.4 (VOUT), U9.5 (VOUT), U15.1 (VIN), U15.3 (EN)
POWAAAA: C28.1, D20.2 (A), Q2.2 (S), U13.6 (SENSE); also elsewhere on the board
bat: C24.1, C25.1, Q2.3 (D), R42.1, U3.2 (VOUT), U13.1 (VIN)

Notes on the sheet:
3.6v
